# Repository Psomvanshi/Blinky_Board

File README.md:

# Blinky_Board
A blinking LED PCB designed using KiCad

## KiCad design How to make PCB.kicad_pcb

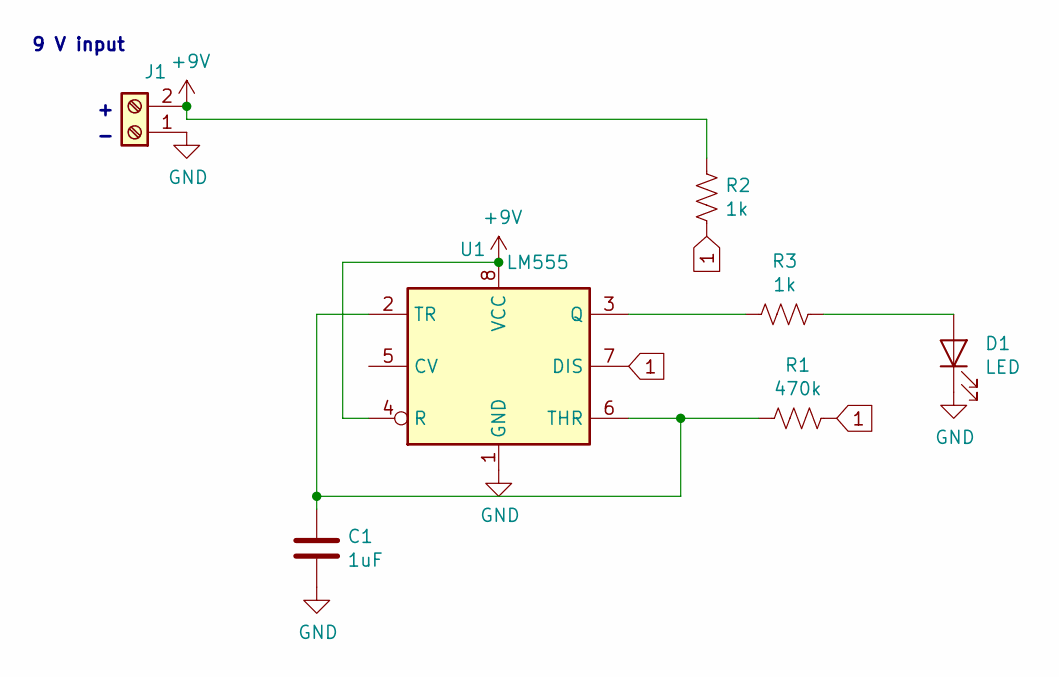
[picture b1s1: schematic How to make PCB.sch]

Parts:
C1: 1uF; C_Disc_D5.0mm_W2.5mm_P2.50mm
D1: LED; LED_D5.0mm
J1: Screw_Terminal_01x02; TerminalBlock_bornier-2_P5.08mm
R1: 470k; R_Axial_DIN0207_L6.3mm_D2.5mm_P10.16mm_Horizontal
R2, R3: 1k; R_Axial_DIN0207_L6.3mm_D2.5mm_P10.16mm_Horizontal
U1: LM555; DIP-8_W7.62mm_LongPads

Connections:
1: R1.1, R2.2, U1.7 (DIS)
+9V: J1.2, R2.1, U1.4 (R), U1.8 (VCC)
GND: C1.2, D1.1 (K), J1.1, U1.1 (GND)
unnamed: C1.1, R1.2, U1.2 (TR), U1.6 (THR)
unnamed: D1.2 (A), R3.1
unnamed: R3.2, U1.3 (Q)

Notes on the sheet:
9 V input

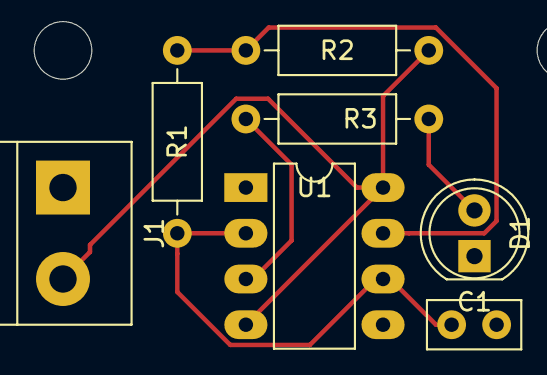
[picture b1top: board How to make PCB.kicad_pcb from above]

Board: 2 copper layers, 7 parts (0 on the bottom side), 6 nets.
